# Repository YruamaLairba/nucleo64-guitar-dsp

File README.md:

# Nucleo guitar DSP

A STM32 Nucleo expansion board to transform your Nucleo board into guitar effect
processor.

## Description

This is a STM32 Nucleo expansion board to turn Nucleo Development board into
a guitar effect processor. It's designed targeting specifically the
nucleo-f441RE board while being usable with other boards, so it may be usable
with most nucleo64 and nucleo144 board.

## Some features:
 * can be used with passive or active guitar, thanks to j4 and j5 selectors
   (mini switches can be used instead of pin headers and jumpers).
   * "norm" is for passive guitar and voltage source below 1vrms. Input
     impedance is ~1 Megohm
   * "pad" is for active source with voltage higher than 1vrms, It apply ~18db
     attenuation. Input impedance is 37 ~ 38kohm.
   * J4 is for left channel and J5 for the right channel. 
 * Stereo input, so it can be used for stuff other than guitar.
 * Output usable with headphone.

## Setup solder bridge

I assume a Nucleo-f411re board. Depending the used Nucleo board, pinout can be
different and things can have different name or may even not exist. Check
various datasheet before doing anything.

JP1 - JP3, connect ADC output to a i2s serial data pin:
 * JP1 connects to PB15 (I2S2_SD)
 * JP2 connects to PB14 (I2S2ext_SD)
 * JP3 connects to PC12 (I2S3_SD)

JP4 - JP6, connect DAC input to a i2s serial data pin:
 * JP4 connects to PB15 (I2S2_SD)
 * JP5 connects to PB14 (I2S2ext_SD)
 * JP6 connects to PC12 (I2S3_SD)

JP7, connect PB13 (I2S2_CK) and PC10 (I2S3_CK), required when I2S3 is used

JP8, connect PB12 (I2S2_WS) and PA4 (I2S3_WS), required when I2S3 is used

Note: only I2S2 peripheral can be used as master.

## Missed consideration
In this first version, i missed or forgot some consideration:

 * **No output to output protection:** it mean boards can be damaged by a wrong
   setup. Putting resistor instead soldebridge on some solder jumper reduce the
risk

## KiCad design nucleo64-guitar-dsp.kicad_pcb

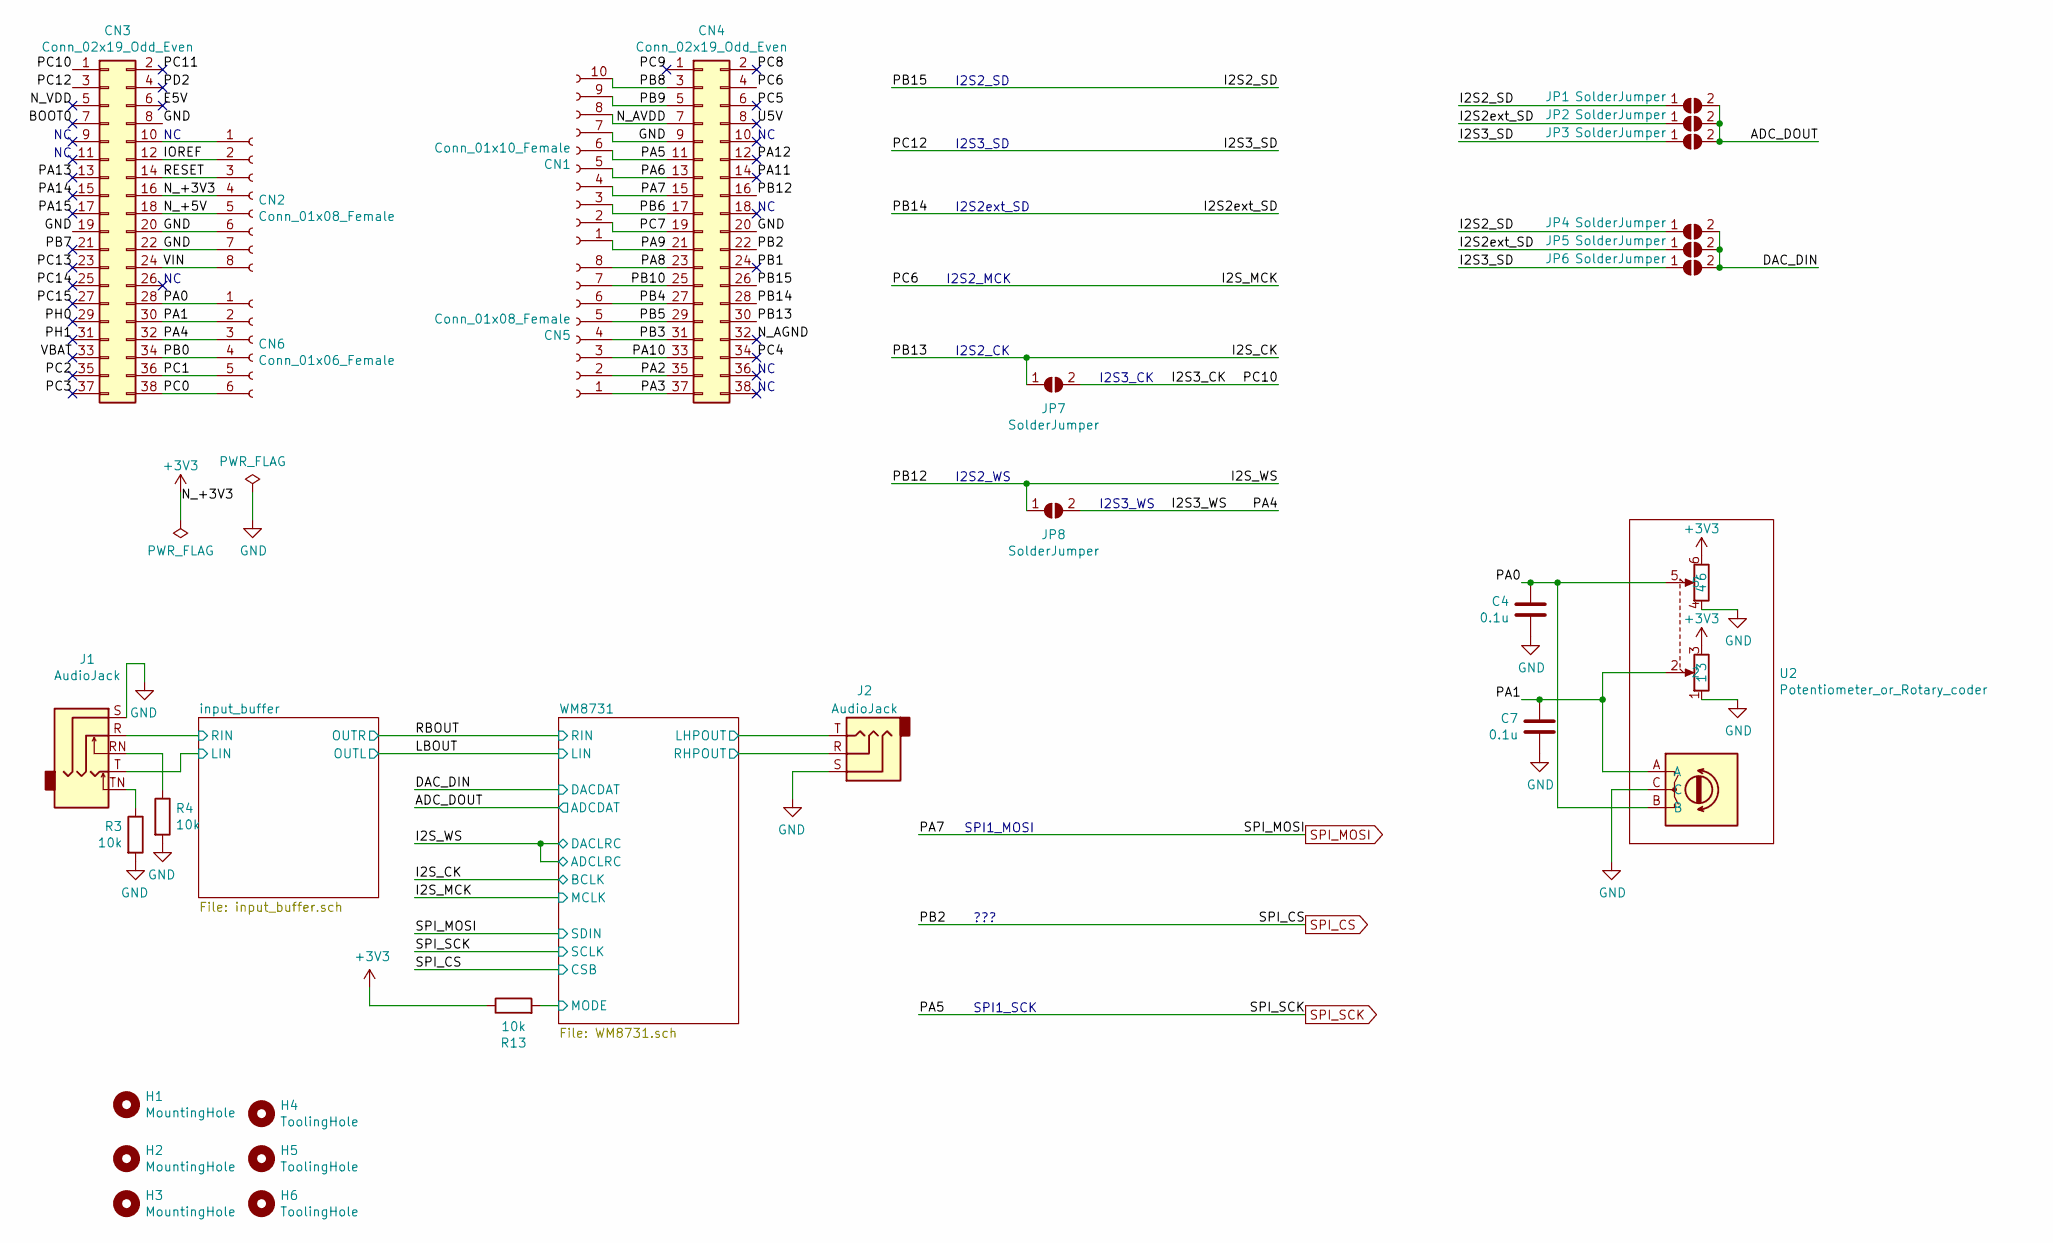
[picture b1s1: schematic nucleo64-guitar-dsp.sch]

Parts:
C4, C7: 0.1u; C_0603_1608Metric_Pad1.08x0.95mm_HandSolder; LCSC Part C14663
CN1: Conn_01x10_Female; PinSocket_1x10_P2.54mm_Vertical
CN2, CN5: Conn_01x08_Female; PinSocket_1x08_P2.54mm_Vertical
CN3, CN4: Conn_02x19_Odd_Even; PinSocket_2x19_P2.54mm_Vertical
CN6: Conn_01x06_Female; PinSocket_1x06_P2.54mm_Vertical
H1, H2, H3: MountingHole; MountingHole_3.2mm_M3_ISO14580
H4, H5, H6: ToolingHole; JLCPCB_2_layer
J1, J2: AudioJack; Jack_6.35mm_Neutrik_NM+NR
JP1, JP2, JP3, JP4, JP5, JP6, JP7, JP8: SolderJumper; SolderJumper-2_P1.3mm_Open_TrianglePad1.0x1.5mm
R3, R4, R13: 10k; R_0603_1608Metric_Pad0.98x0.95mm_HandSolder; LCSC Part C25804
U2: Potentiometer_or_Rotary_coder; Potentiometer_or_Rotary_Encoder

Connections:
+3V3: CN2.4, CN3.16, R13.1, U2.3, U2.6; also elsewhere on the board
/ADC_DOUT: JP1.2 (B), JP2.2 (B), JP3.2 (B); also elsewhere on the board
/BOOT0: CN3.7
/DAC_DIN: JP4.2 (B), JP5.2 (B), JP6.2 (B); also elsewhere on the board
/E5V: CN3.6
/I2S2_SD: CN4.26, JP1.1 (A), JP4.1 (A)
/I2S2ext_SD: CN4.28, JP2.1 (A), JP5.1 (A)
/I2S3_CK: CN3.1, JP7.2 (B)
/I2S3_SD: CN3.3, JP3.1 (A), JP6.1 (A)
/I2S3_WS: CN3.32, CN6.3, JP8.2 (B)
/I2S_CK: CN4.30, JP7.1 (A); also elsewhere on the board
/I2S_MCK: CN4.4; also elsewhere on the board
/I2S_WS: CN4.16, JP8.1 (A); also elsewhere on the board
/IOREF: CN2.2, CN3.12
/N_+5V: CN2.5, CN3.18
/N_AGND: CN4.32
/N_AVDD: CN1.8, CN4.7
/N_VDD: CN3.5
/PA0: C4.1, CN3.28, CN6.1, U2.5, U2.B
/PA1: C7.1, CN3.30, CN6.2, U2.2, U2.A
/PA2: CN4.35, CN5.2
/PA3: CN4.37, CN5.1
/PA6: CN1.5, CN4.13
/PA8: CN4.23, CN5.8
/PA9: CN1.1, CN4.21
/PA10: CN4.33, CN5.3
/PA11: CN4.14
/PA12: CN4.12
/PA13: CN3.13
/PA14: CN3.15
/PA15: CN3.17
/PB0: CN3.34, CN6.4
/PB1: CN4.24
/PB3: CN4.31, CN5.4
/PB4: CN4.27, CN5.6
/PB5: CN4.29, CN5.5
/PB6: CN1.3, CN4.17
/PB7: CN3.21
/PB8: CN1.10, CN4.3
/PB9: CN1.9, CN4.5
/PB10: CN4.25, CN5.7
/PC0: CN3.38, CN6.6
/PC1: CN3.36, CN6.5
/PC2: CN3.35
/PC3: CN3.37
/PC4: CN4.34
/PC5: CN4.6
/PC7: CN1.2, CN4.19
/PC8: CN4.2
/PC9: CN4.1
/PC11: CN3.2
/PC13: CN3.23
/PC14: CN3.25
/PC15: CN3.27
/PD2: CN3.4
/PH0: CN3.29
/PH1: CN3.31
/RESET: CN2.3, CN3.14
/U5V: CN4.8
/VBAT: CN3.33
/VIN: CN2.8, CN3.24
/WM8731/LHPOUT: J2.T; also elsewhere on the board
/WM8731/MODE: R13.2; also elsewhere on the board
/WM8731/RHPOUT: J2.R; also elsewhere on the board
/input_buffer/LIN: J1.T; also elsewhere on the board
/input_buffer/RIN: J1.R; also elsewhere on the board
GND: C4.2, C7.2, CN1.7, CN2.6, CN2.7, CN3.8, CN3.19, CN3.20, CN3.22, CN4.9, CN4.20, J1.S, J2.S, R3.2, R4.2, U2.1, U2.4, U2.C; also elsewhere on the board
unnamed: CN2.1, CN3.10
unnamed: J1.RN, R4.1
unnamed: J1.TN, R3.1
SPI_CS: CN4.22; also elsewhere on the board
SPI_MOSI: CN1.4, CN4.15; also elsewhere on the board
SPI_SCK: CN1.6, CN4.11; also elsewhere on the board

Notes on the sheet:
I2S2_WS
I2S2_CK
I2S2ext_SD
I2S2_SD
I2S2_MCK
I2S3_WS
I2S3_CK
I2S3_SD
SPI1_SCK
???
SPI1_MOSI

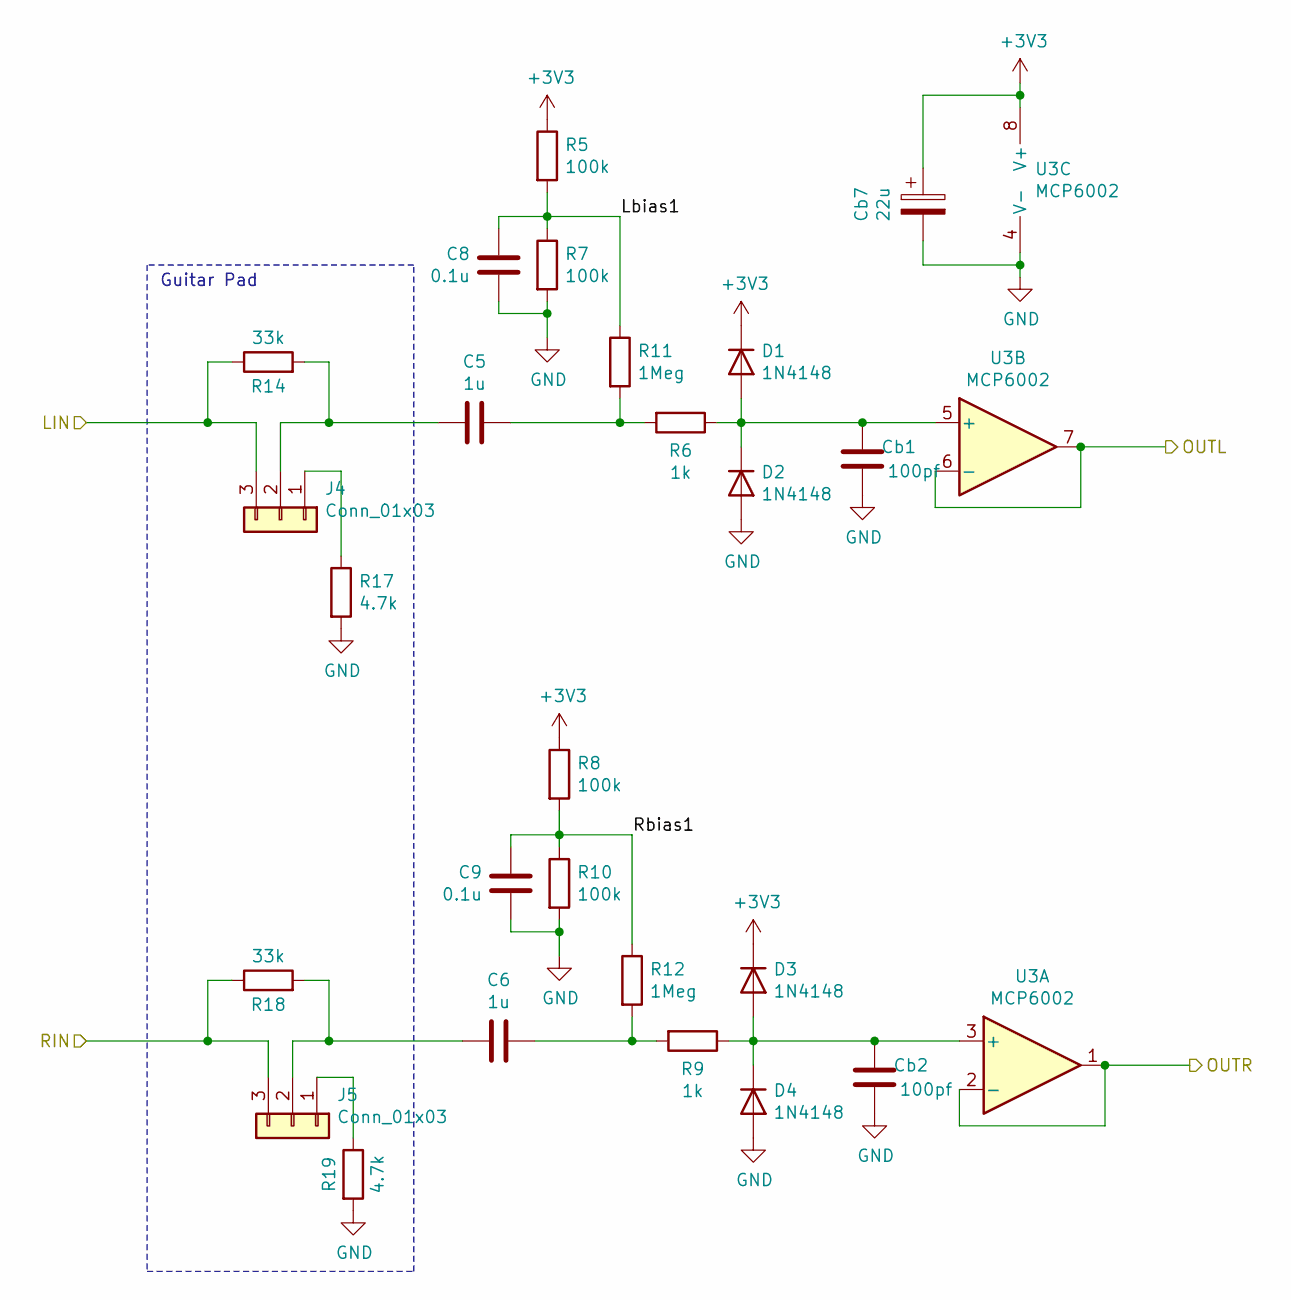
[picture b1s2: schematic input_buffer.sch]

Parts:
C5, C6: 1u; C_1206_3216Metric_Pad1.33x1.80mm_HandSolder; LCSC Part C1848
C8, C9: 0.1u; C_0603_1608Metric_Pad1.08x0.95mm_HandSolder; LCSC Part C14663
Cb1, Cb2: 100pf; C_0603_1608Metric_Pad1.08x0.95mm_HandSolder; LCSC Part C14858
Cb7: 22u; C_0805_2012Metric_Pad1.18x1.45mm_HandSolder; LCSC Part C45783
D1, D2, D3, D4: 1N4148; D_SOD-123; LCSC Part C81598
J4, J5: Conn_01x03; PinHeader_1x03_P2.54mm_Vertical
R5, R7, R8, R10: 100k; R_0603_1608Metric_Pad0.98x0.95mm_HandSolder; LCSC Part C22938
R6, R9: 1k; R_0603_1608Metric_Pad0.98x0.95mm_HandSolder; LCSC Part C21190
R11, R12: 1Meg; R_0603_1608Metric_Pad0.98x0.95mm_HandSolder; LCSC Part C22935
R14, R18: 33k; R_0603_1608Metric_Pad0.98x0.95mm_HandSolder; LCSC Part C4216
R17, R19: 4.7k; R_0603_1608Metric_Pad0.98x0.95mm_HandSolder; LCSC Part C23162
U3: MCP6002; SOIC-8_3.9x4.9mm_P1.27mm; LCSC Part C7377

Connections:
+3V3: Cb7.1, D1.1 (K), D3.1 (K), R5.1, R8.1, U3.8 (V+); also elsewhere on the board
/LBOUT: U3.6 (-), U3.7; also elsewhere on the board
/RBOUT: U3.1, U3.2 (-); also elsewhere on the board
/input_buffer/LIN: J4.3, R14.1; also elsewhere on the board
/input_buffer/Lbias1: C8.1, R5.2, R7.1, R11.1
/input_buffer/RIN: J5.3, R18.1; also elsewhere on the board
/input_buffer/Rbias1: C9.1, R8.2, R10.1, R12.1
GND: C8.2, C9.2, Cb1.1, Cb2.1, Cb7.2, D2.2 (A), D4.2 (A), R7.2, R10.2, R17.2, R19.2, U3.4 (V-); also elsewhere on the board
unnamed: C5.1, R6.2, R11.2
unnamed: C5.2, J4.2, R14.2
unnamed: C6.1, R9.2, R12.2
unnamed: C6.2, J5.2, R18.2
unnamed: Cb1.2, D1.2 (A), D2.1 (K), R6.1, U3.5 (+)
unnamed: Cb2.2, D3.2 (A), D4.1 (K), R9.1, U3.3 (+)
unnamed: J4.1, R17.1
unnamed: J5.1, R19.1

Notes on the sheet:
Guitar Pad

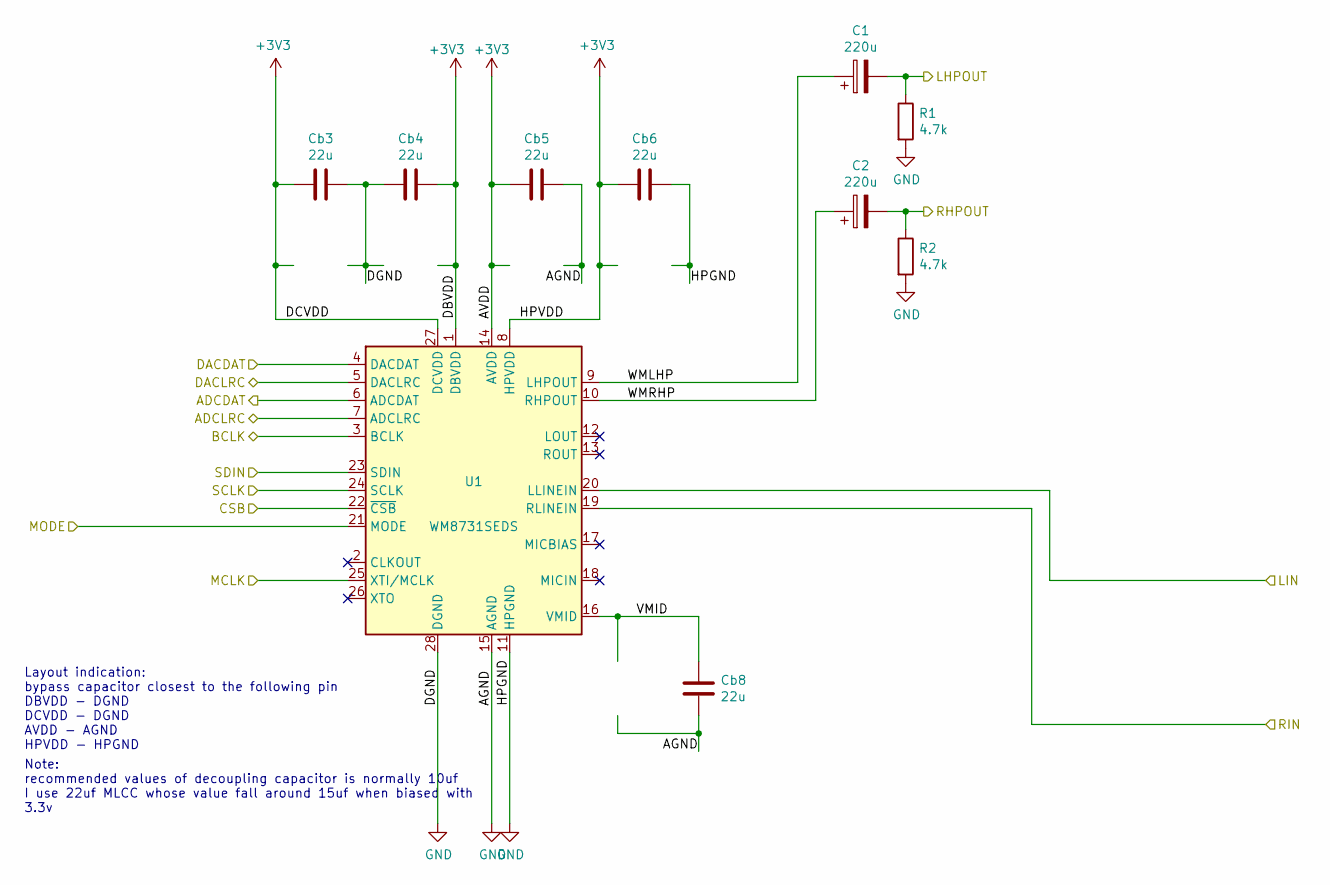
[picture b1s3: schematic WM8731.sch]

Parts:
C1, C2: 220u; CP_Elec_6.3x7.7; LCSC Part C127968
Cb3, Cb4, Cb5, Cb6, Cb8: 22u; C_0805_2012Metric_Pad1.18x1.45mm_HandSolder; LCSC Part C45783
R1, R2: 4.7k; R_0603_1608Metric_Pad0.98x0.95mm_HandSolder; LCSC Part C23162
U1: WM8731SEDS; SSOP-28_5.3x10.2mm_P0.65mm; LCSC Part C323837

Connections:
+3V3: Cb3.1, Cb4.1, Cb5.1, Cb6.1, U1.1 (DBVDD), U1.8 (HPVDD), U1.14 (AVDD), U1.27 (DCVDD); also elsewhere on the board
/ADC_DOUT: U1.6 (ADCDAT); also elsewhere on the board
/DAC_DIN: U1.4 (DACDAT); also elsewhere on the board
/I2S_CK: U1.3 (BCLK); also elsewhere on the board
/I2S_MCK: U1.25 (XTI/MCLK); also elsewhere on the board
/I2S_WS: U1.5 (DACLRC), U1.7 (ADCLRC); also elsewhere on the board
/LBOUT: U1.20 (LLINEIN); also elsewhere on the board
/RBOUT: U1.19 (RLINEIN); also elsewhere on the board
/WM8731/LHPOUT: C1.2, R1.1; also elsewhere on the board
/WM8731/MODE: U1.21 (MODE); also elsewhere on the board
/WM8731/RHPOUT: C2.2, R2.1; also elsewhere on the board
/WM8731/VMID: Cb8.1, U1.16 (VMID)
/WM8731/WMLHP: C1.1, U1.9 (LHPOUT)
/WM8731/WMRHP: C2.1, U1.10 (RHPOUT)
GND: Cb3.2, Cb4.2, Cb5.2, Cb6.2, Cb8.2, R1.2, R2.2, U1.11 (HPGND), U1.15 (AGND), U1.28 (DGND); also elsewhere on the board
SPI_CS: U1.22 (~CSB); also elsewhere on the board
SPI_MOSI: U1.23 (SDIN); also elsewhere on the board
SPI_SCK: U1.24 (SCLK); also elsewhere on the board

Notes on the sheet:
Layout indication: bypass capacitor closest to the following pin DBVDD - DGND DCVDD - DGND AVDD - AGND HPVDD - HPGND
Note: recommended values of decoupling capacitor is normally 10uf I use 22uf MLCC whose value fall around 15uf when biased with 3.3v

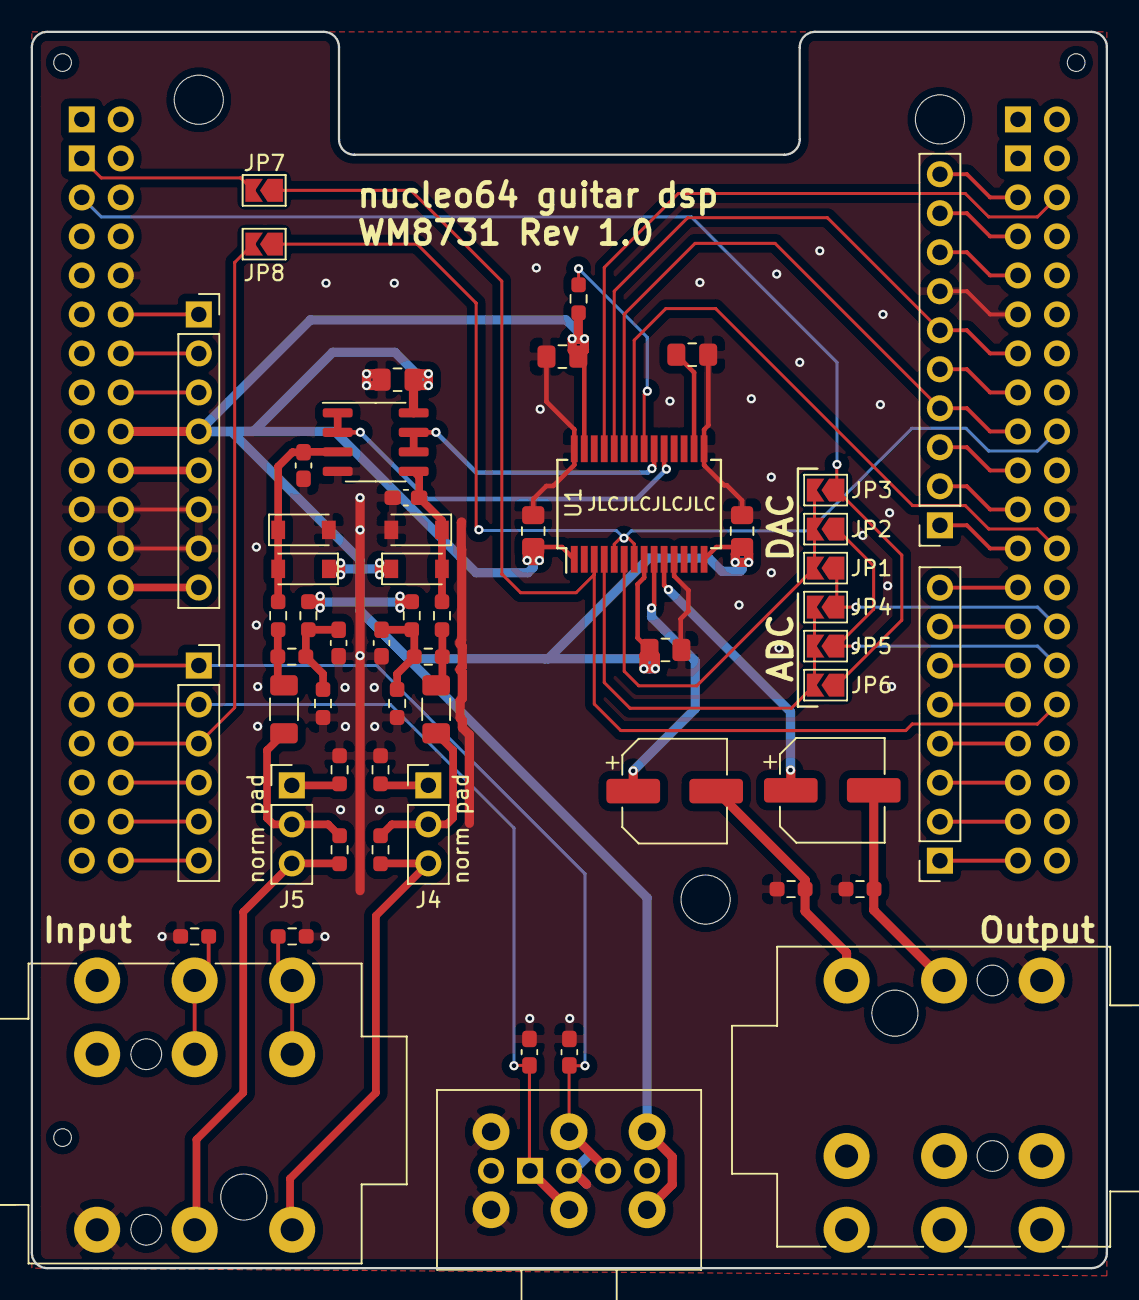
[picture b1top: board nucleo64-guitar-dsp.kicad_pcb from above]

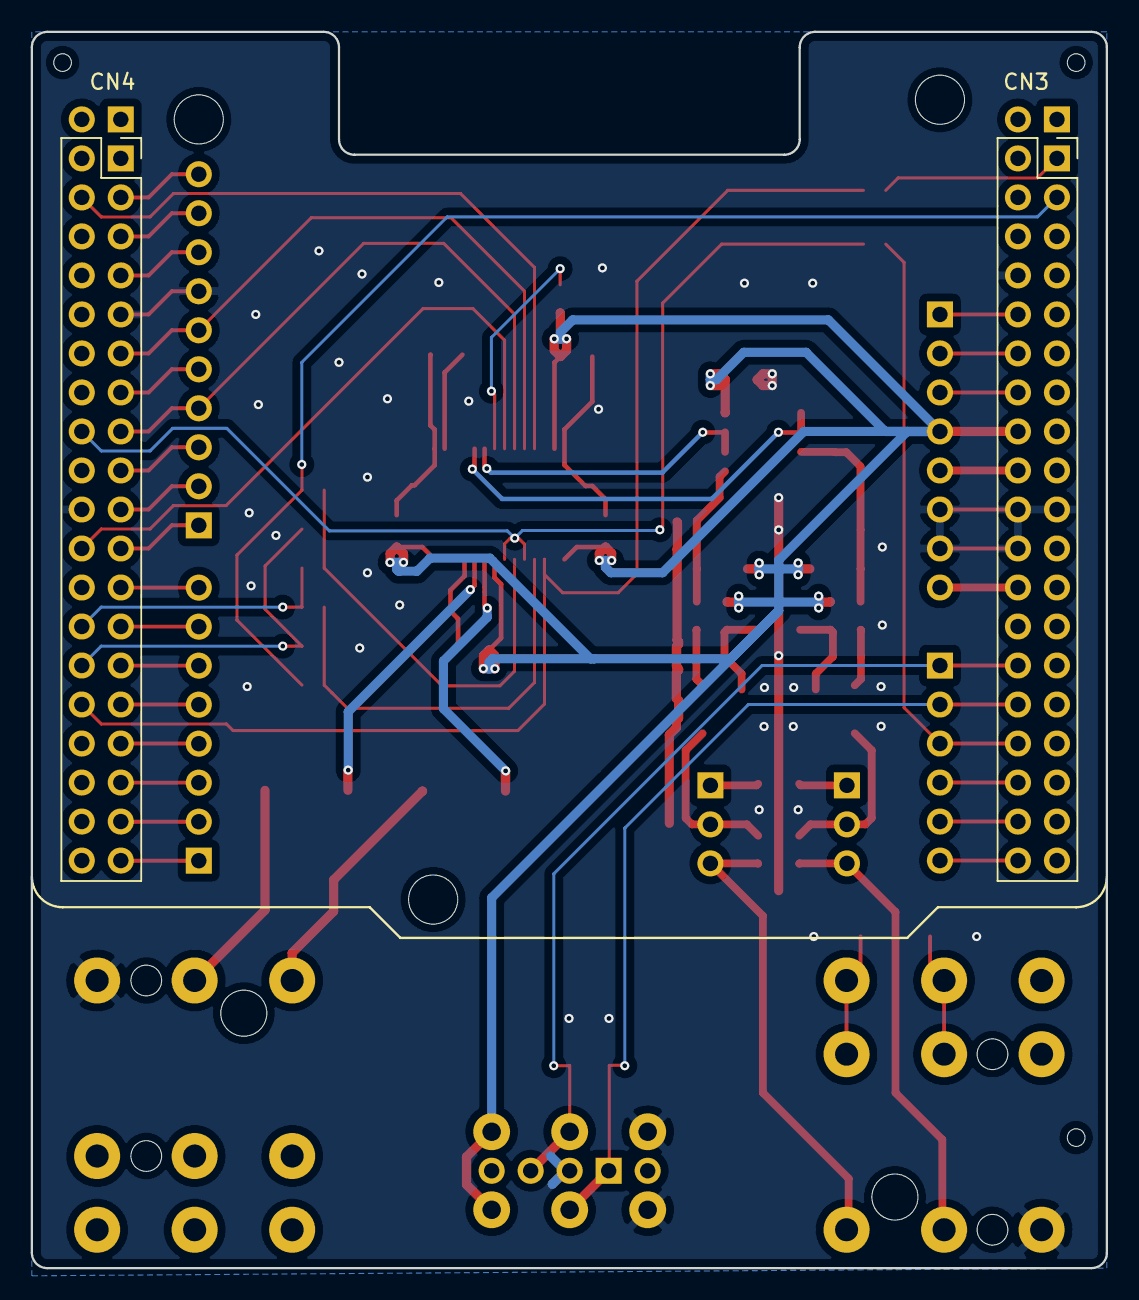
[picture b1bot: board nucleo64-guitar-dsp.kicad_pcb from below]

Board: 4 copper layers, 70.0 x 80.5 mm, 64 parts (6 on the bottom side), 62 nets.

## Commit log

2021-07-24 squashing crappy history
